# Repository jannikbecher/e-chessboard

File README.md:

# E-Chessboard
Trying to build a e-chessboard similiar to the Regium

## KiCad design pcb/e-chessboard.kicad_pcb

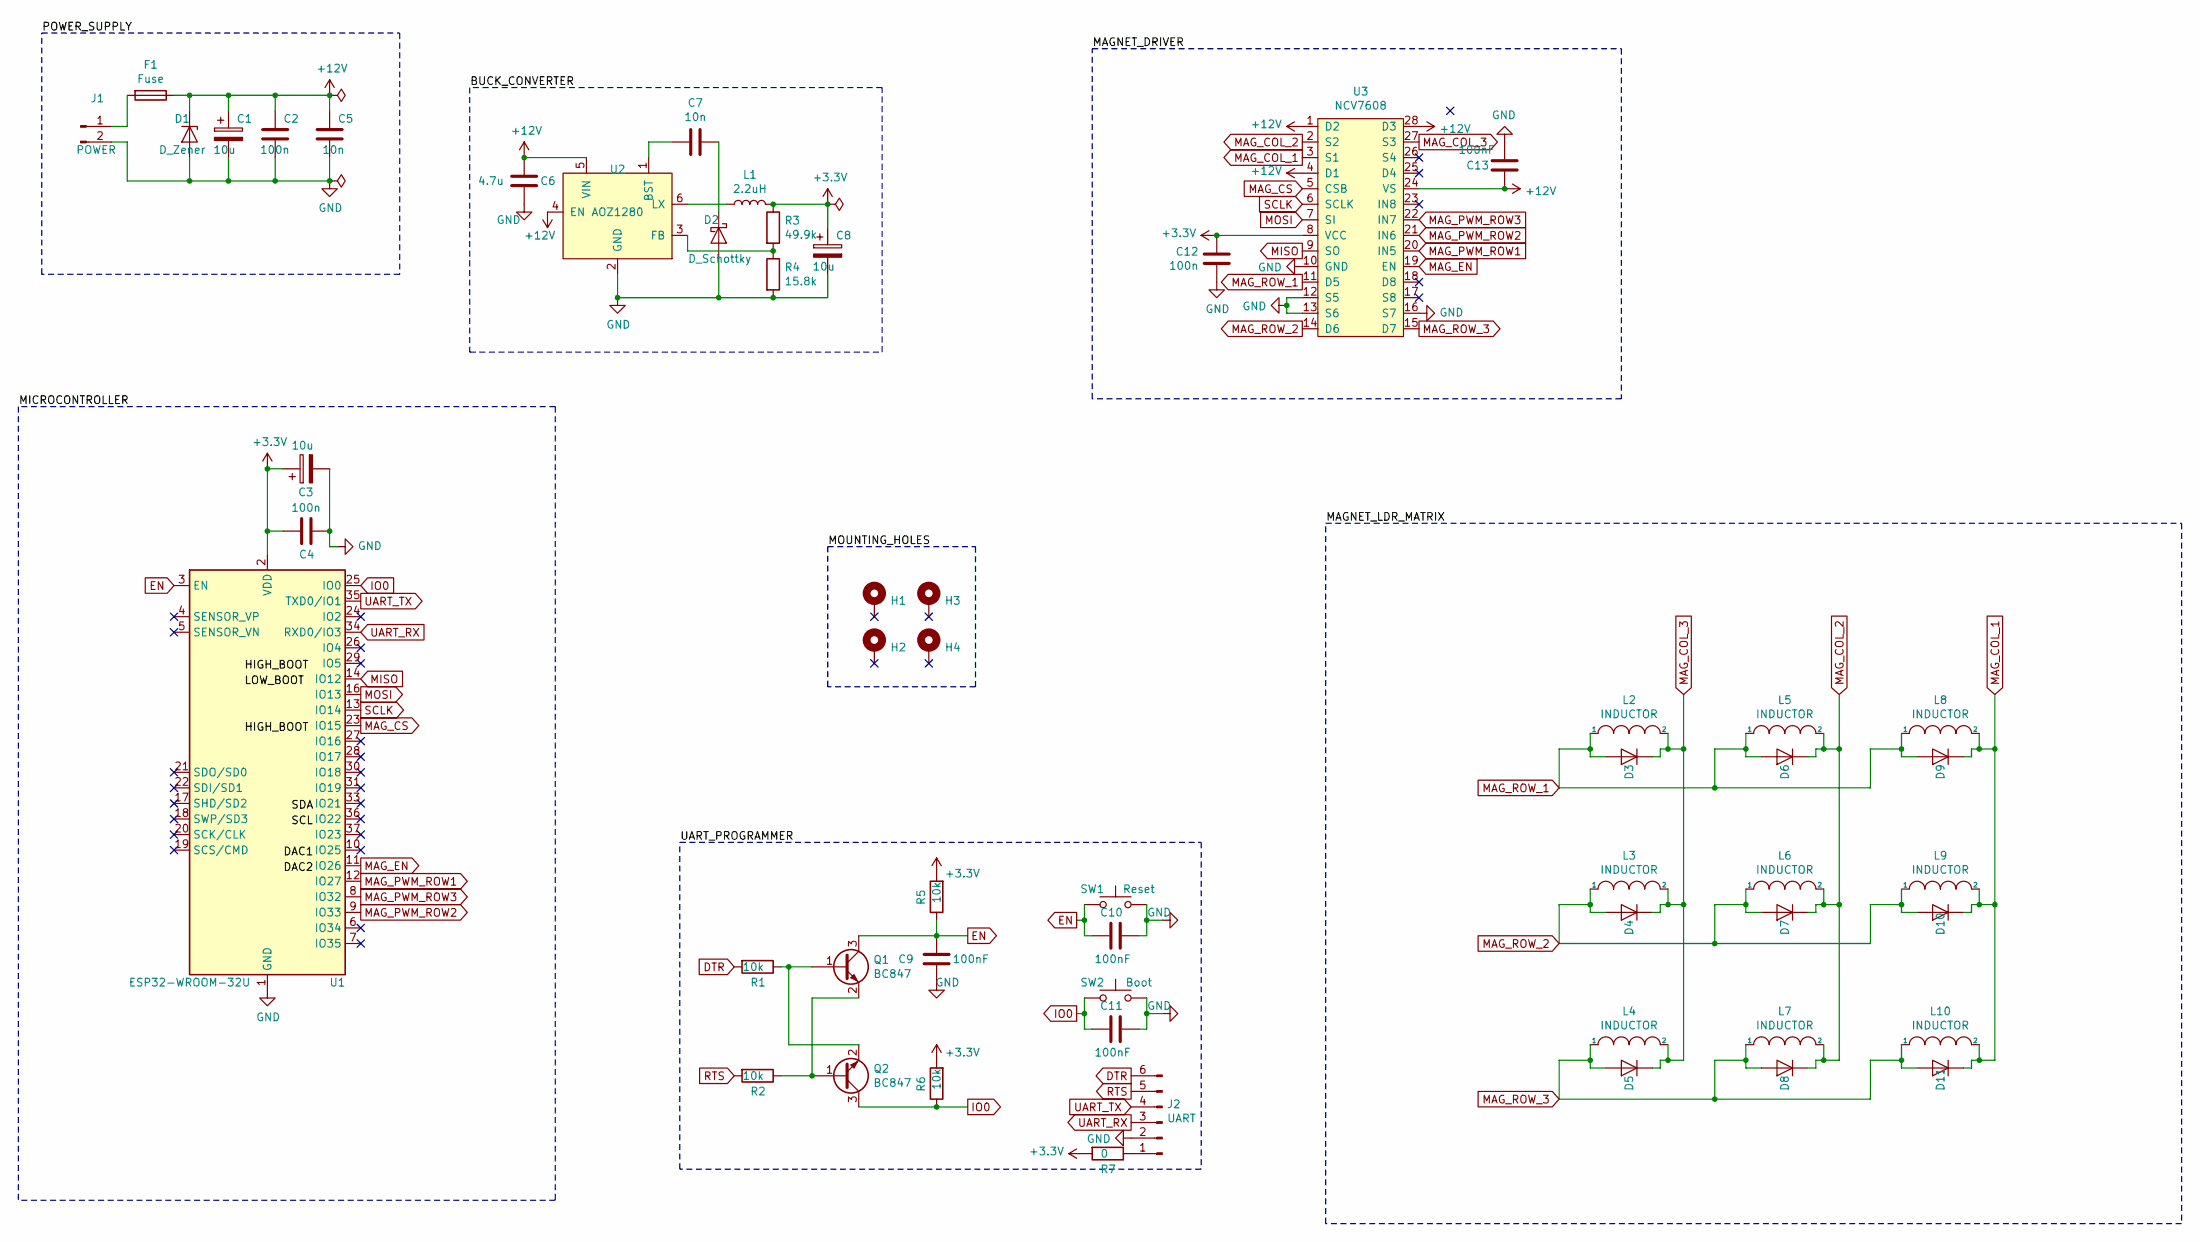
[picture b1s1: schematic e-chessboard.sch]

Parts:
C1, C3, C8: 10u; CP_EIA-3528-21_Kemet-B
C2, C4, C12: 100n; C_0805_2012Metric_Pad1.15x1.40mm_HandSolder
C5, C7: 10n; C_0805_2012Metric_Pad1.15x1.40mm_HandSolder
C6: 4.7u; C_0805_2012Metric_Pad1.15x1.40mm_HandSolder
C9, C10, C11, C13: 100nF; C_0805_2012Metric_Pad1.15x1.40mm_HandSolder
D1: D_Zener; D_SMA
D2: D_Schottky; D_SOD-123
D3, D4, D5, D6, D7, D8, D9, D10, D11: D; D_SMA
F1: Fuse; Fuseholder_Cylinder-5x20mm_Schurter_0031_8201_Horizontal_Op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
H1, H2, H3, H4: MountingHole_Pad; MountingHole_3.2mm_M3_ISO7380_Pad
J1: POWER; BarrelJack_CUI_PJ-102AH_Horizontal
J2: UART; PinHeader_2x03_P2.54mm_Vertical
L1: 2.2uH; L_Bourns-SRN4018
L2, L3, L4, L5, L6, L7, L8, L9, L10: INDUCTOR; 20_15_electromagnet
Q1, Q2: BC847; SOT-23
R1, R2, R5, R6: 10k; R_0805_2012Metric
R3: 49.9k; R_0805_2012Metric
R4: 15.8k; R_0805_2012Metric
R7: 0; R_0805_2012Metric
SW1: Reset; SW_SPST_EVQPE1
SW2: Boot; SW_SPST_EVQPE1
U1: ESP32-WROOM-32U
U2: AOZ1280; SOT-23-6
U3: NCV7608; SOIC-28W_7.5x17.9mm_P1.27mm

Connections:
+3V3: C3.1, C4.2, C8.1, C12.2, L1.2, R3.1, R5.2, R6.2, R7.2, U1.2 (VDD), U3.8 (VCC)
+12V: C1.1, C2.1, C5.1, C6.1, C13.2, D1.1 (K), F1.1, U2.4 (EN), U2.5 (VIN), U3.1 (D2), U3.4 (D1), U3.24 (VS), U3.28 (D3)
DTR: J2.6, R1.2
EN: C9.1, C10.2, Q1.3 (C), R5.1, SW1.1, U1.3 (EN)
GND: C1.2, C2.2, C3.2, C4.1, C5.2, C6.2, C8.2, C9.2, C10.1, C11.1, C12.1, C13.1, D1.2 (A), D2.2 (A), J1.2, J2.2, R4.2, SW1.2, SW2.2, U1.1 (GND), U1.15 (GND), U1.38 (GND), U1.39 (GND), U2.2 (GND), U3.10 (GND), U3.12 (S5), U3.13 (S6), U3.16 (S7)
IO0: C11.2, Q2.3 (C), R6.1, SW2.1, U1.25 (IO0)
MAG_COL_1: D9.1 (K), D10.1 (K), D11.1 (K), L8.2, L9.2, L10.2, U3.3 (S1)
MAG_COL_2: D6.1 (K), D7.1 (K), D8.1 (K), L5.2, L6.2, L7.2, U3.2 (S2)
MAG_COL_3: D3.1 (K), D4.1 (K), D5.1 (K), L2.2, L3.2, L4.2, U3.27 (S3)
MAG_CS: U1.23 (IO15), U3.5 (CSB)
MAG_EN: U1.11 (IO26), U3.19 (EN)
MAG_PWM_ROW1: U1.12 (IO27), U3.20 (IN5)
MAG_PWM_ROW2: U1.9 (IO33), U3.21 (IN6)
MAG_PWM_ROW3: U1.8 (IO32), U3.22 (IN7)
MAG_ROW_1: D3.2 (A), D6.2 (A), D9.2 (A), L2.1, L5.1, L8.1, U3.11 (D5)
MAG_ROW_2: D4.2 (A), D7.2 (A), D10.2 (A), L3.1, L6.1, L9.1, U3.14 (D6)
MAG_ROW_3: D5.2 (A), D8.2 (A), D11.2 (A), L4.1, L7.1, L10.1, U3.15 (D7)
MISO: U1.14 (IO12), U3.9 (SO)
MOSI: U1.16 (IO13), U3.7 (SI)
unnamed: C7.1, D2.1 (K)
unnamed: C7.2, U2.1 (BST)
unnamed: F1.2, J1.1
unnamed: J2.1, R7.1
unnamed: L1.1, U2.6 (LX)
unnamed: Q1.1 (B), Q2.2 (E), R1.1
unnamed: Q1.2 (E), Q2.1 (B), R2.1
unnamed: R3.2, R4.1, U2.3 (FB)
RTS: J2.5, R2.2
SCLK: U1.13 (IO14), U3.6 (SCLK)
UART_RX: J2.3, U1.34 (RXD0/IO3)
UART_TX: J2.4, U1.35 (TXD0/IO1)

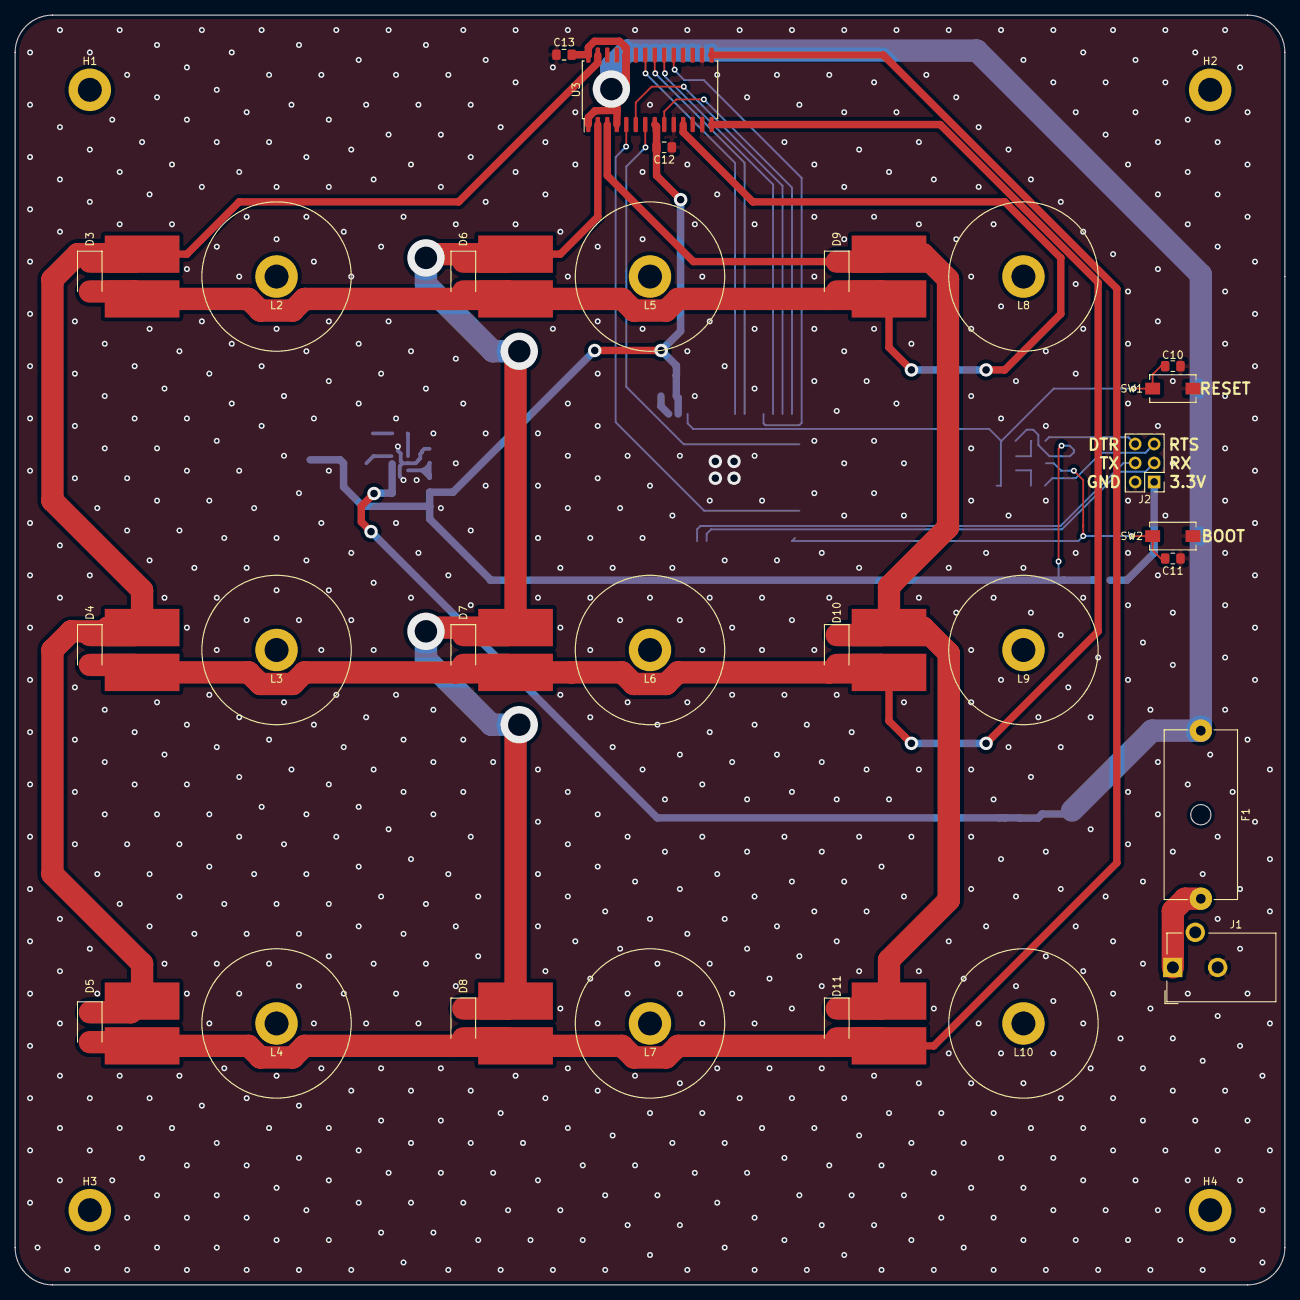
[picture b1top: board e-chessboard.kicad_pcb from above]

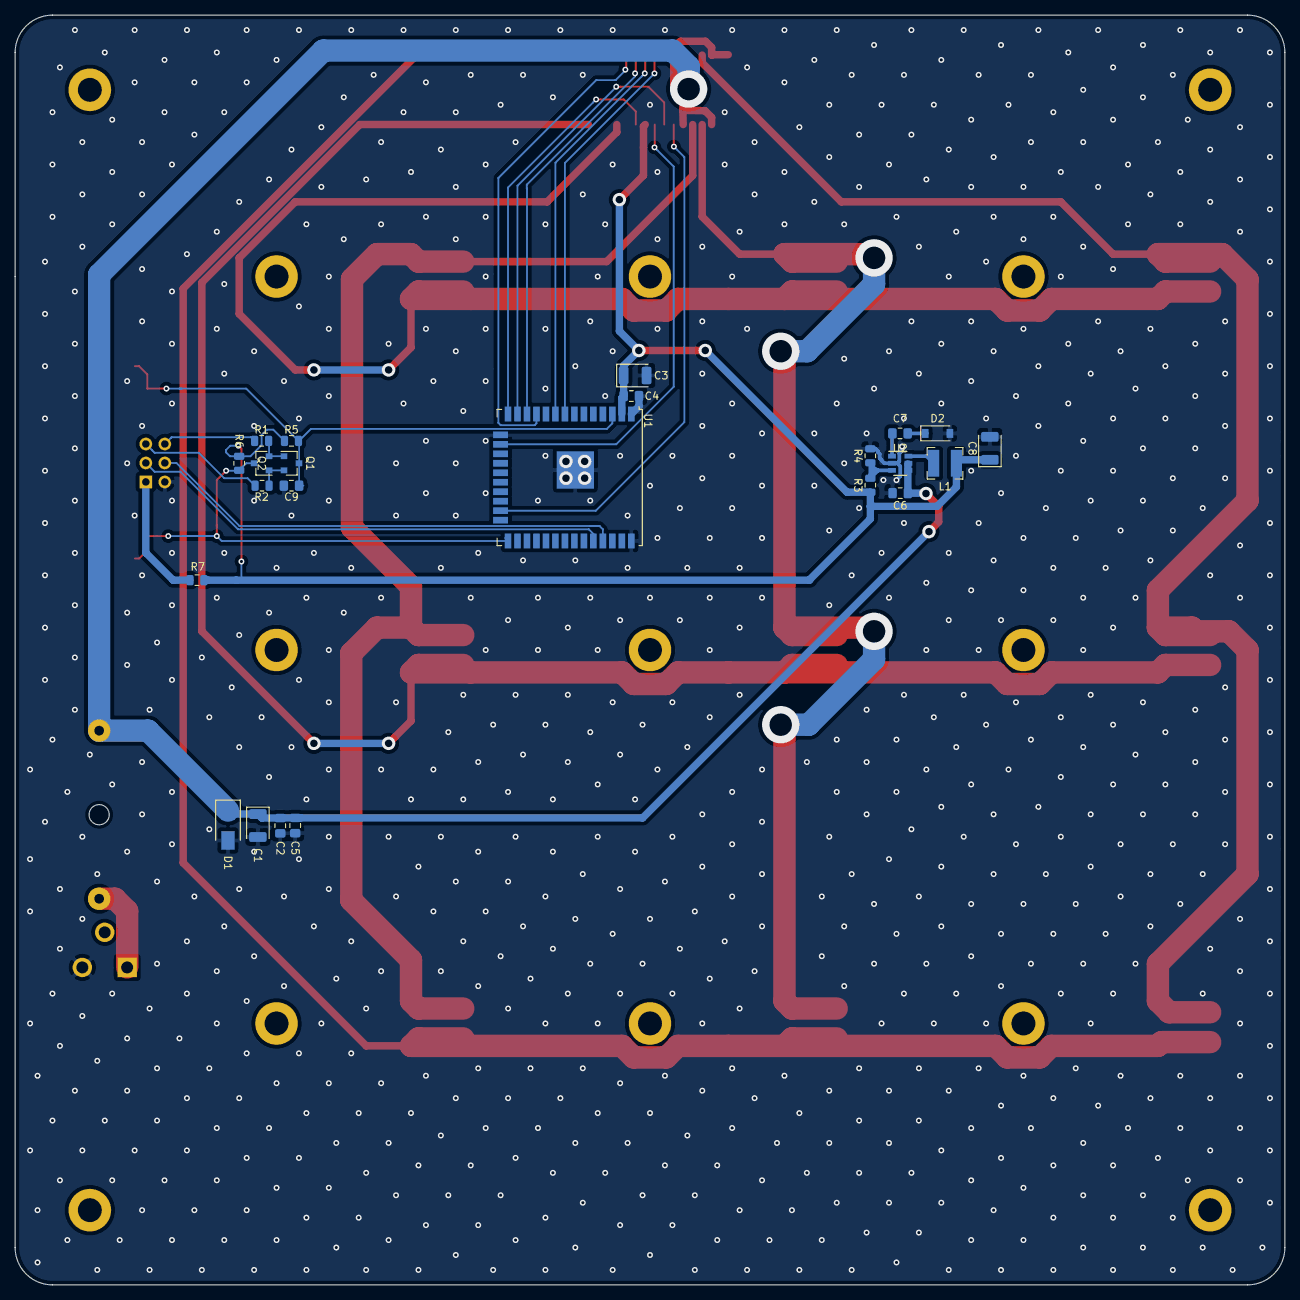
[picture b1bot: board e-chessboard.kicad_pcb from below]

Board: 2 copper layers, 170.0 x 170.0 mm, 55 parts (23 on the bottom side), 31 nets.

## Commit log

2020-02-28 init kicad
2020-02-28 feat(kicad): adding library structure
    adding a library structure as descriped in https://hackaday.com/2017/05/18/kicad-best-practises-library-management/
2020-02-28 feature(kicad): adding footprint
    Adding new symbol for NCV7680 and AOZ1280.
    Adding new footprint for 20/15 electromaget (not finished yet).
2020-02-28 feat(kicad): adding power circuit
    Adding easy power supply with capacitors. Reverse diode is missing..
2020-02-28 feat(kicad): adding buck converter
    Adding AOZ1280 buck converter to convert 12V to 3.3V.
2020-02-28 feat(kicad): adding magnet matrix and driver
    Adding the 3x3 magnet matrix and the NCV7608 driver.
2020-02-28 fix(kicad): adding missing footprints
    Adding C, R, L, D footprints
2020-02-28 feat(kicad): adding uart programmer
    Adding the UART programmer to the eps32.
2020-02-28 feat(kicad): Adding connections to ESP32
    Connecting everything together, putting pull-up/downs for spi to the
    esp32, powering the esp32.
2020-02-28 fix(kicad): adding diodes to magnets
    Adding missing reverse current diodes to the magnets.
2020-02-28 fix(kicad): Updating electromagnet footprint
    Electromagnet has now a M3 mounting hole after ISO norm.
2020-02-29 feat(kicad): Tidy up schematic
    Adding blueboxes to schematic parts.
2020-02-29 feat(kicad): Adding mounting holes
    Adding four M3 mounting holes.
2020-02-29 feat(kicad): adding netclass design rules
    Adding fundamental design rules:
    - trace width
    - via size
    - 4-layer board
2020-02-29 fix(kicad): removing pull-up/down resistors
    Removing pull-up/down resistors for spi and pwm. I'm using the build in
    ones for simplification.
2020-02-29 feat(kicad): adding ldr sensors
    Adding ldr sensors to the matrix for checking the location of the chess
    pieces.
2020-03-02 feat(kicad): generating netlist
    Fixing all erc issues, adding power and fuse footprints and generating
    netlist.
2020-03-02 feat(kicad): designing pcbnew
    Positioning all magnets and mounting holes.
2020-03-02 feat(kicad): positioning power circuit and uart
2020-03-02 feat(kicad): placing all components
    Placing all components to their places.
2020-03-02 fix(kicad): redesign pcb
    Removing outlayer to decrease the pcb size.
2020-03-03 fix(kicad): adding more traces
    Adding traces and changing some schematic outputs for optimization.
2020-03-03 fix(kicad): laying all spi traces
2020-03-03 fix(kicad): fixing all erc error and warnings
    Ready for first release!!!
2020-03-03 fix(kicad): adding label for taster and uart
2020-03-03 feat(esp32): adding scripts for uploading code to the mc
    Adding previous written scripts for uploading code to the esp32.
2020-03-03 fix(kicad): fixing wrong ldr lineup in the matrix
    Fixing issue #2. Pcb not updated yet.
2020-03-03 fix(kicad): fixing ldr issue
    Still not 100% sure weather this is working.
    Tried to fix #2.
2020-03-04 fix(kicad): redesign pcb
    Redesigning the pcb with the new ldr matrix.
    I'm pretty sure, that's it's still not working, but for the first
    prototype I will put the focus on the magnets and not the ldr. Just a
    prove a concept.
2020-03-06 feat(kicad): adding gerber files
    Adding gerber files and finishing the first release.
2020-03-06 feat(kicad): removing ldr for simplification
    Removing the ldr matrix for simplification. I had to switch to a two
    layer board beacause of the price. See #3
2020-03-06 fix(kicad): fixing magnet matrix
    Had some short circuits in the magnet matrix.
2020-03-06 feat(kicad): adding annotation
    Adding annotation for the components.
2020-03-06 feat(kicad): switching to 2 layer board
    Deleting every compoenent and switching from 4 layer to 2 layer.
2020-03-06 feat(kicad): placing all components and drawing wires
    Placing all components and laying the wires for the 3x3 magnet matrix.
2020-03-06 fix(kicad): fixing pin order of pwm
    Adjusting the pin order of the pwm lines for better line laying.
2020-03-06 feat(kicad): wireing mosfet driver
    Completly wirering the mosfet driver ic.
2020-03-06 feat(kicad): adding 0R resistor for programmer safty
    Adding a zero ohm resistor between the buck converter and the progrmamer
    3.3v line for safty reasons.
2020-03-07 feat(kicad): laying all traces
    Laying all missing traces. Next step: via stitching
2020-03-07 feat(kicad): adding via stictes
    Adding 0.8/0.4 via stitching.
2020-03-07 feat(kicad): adding gerber files
